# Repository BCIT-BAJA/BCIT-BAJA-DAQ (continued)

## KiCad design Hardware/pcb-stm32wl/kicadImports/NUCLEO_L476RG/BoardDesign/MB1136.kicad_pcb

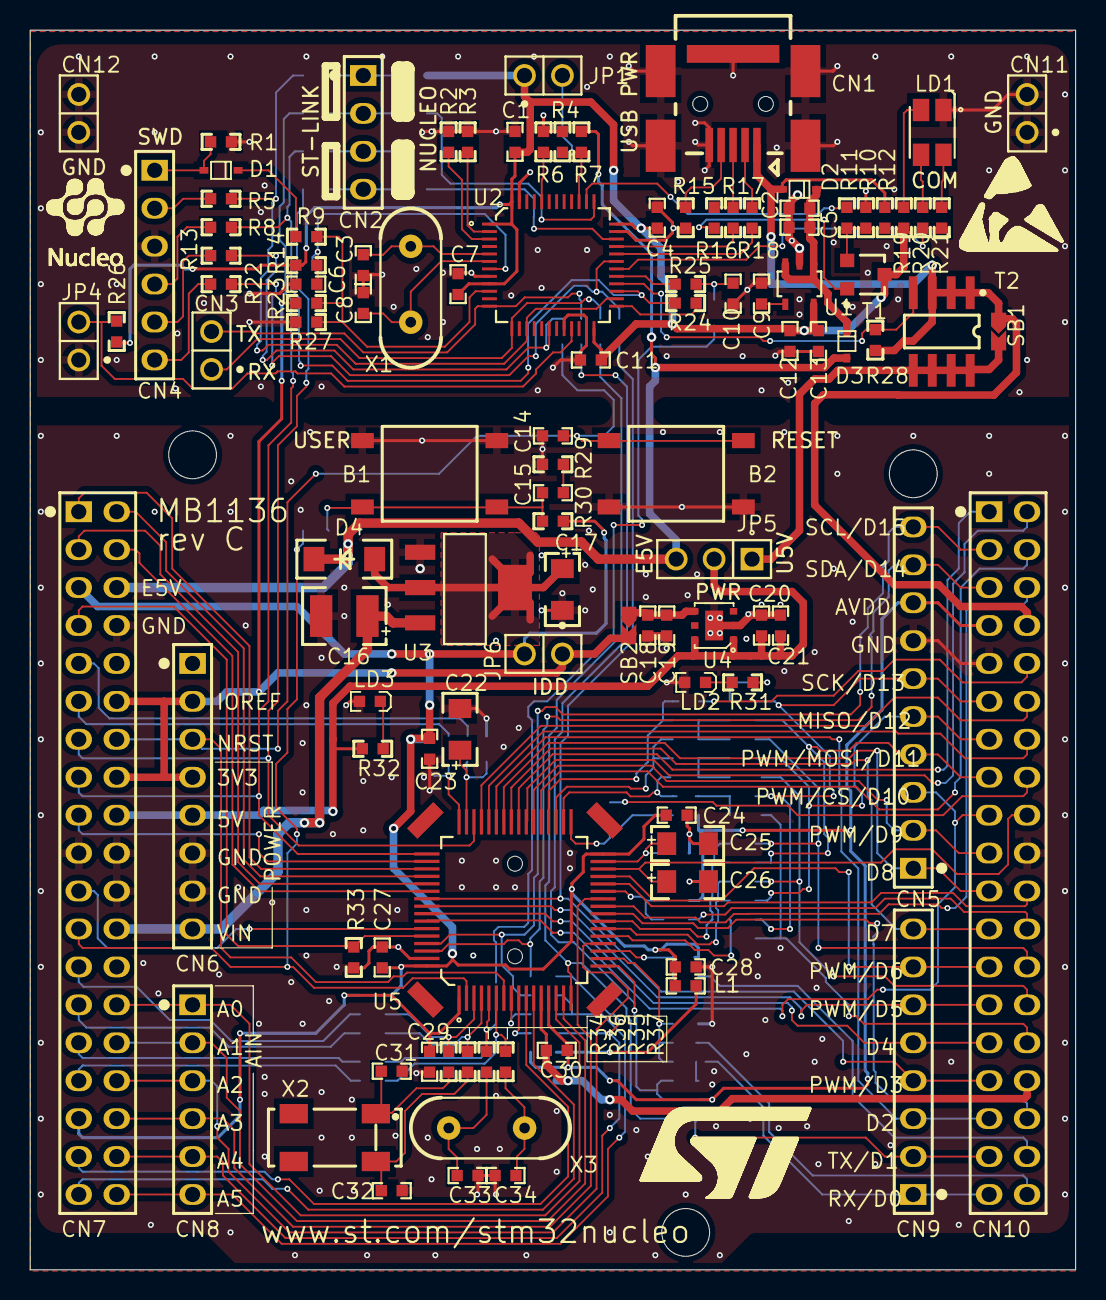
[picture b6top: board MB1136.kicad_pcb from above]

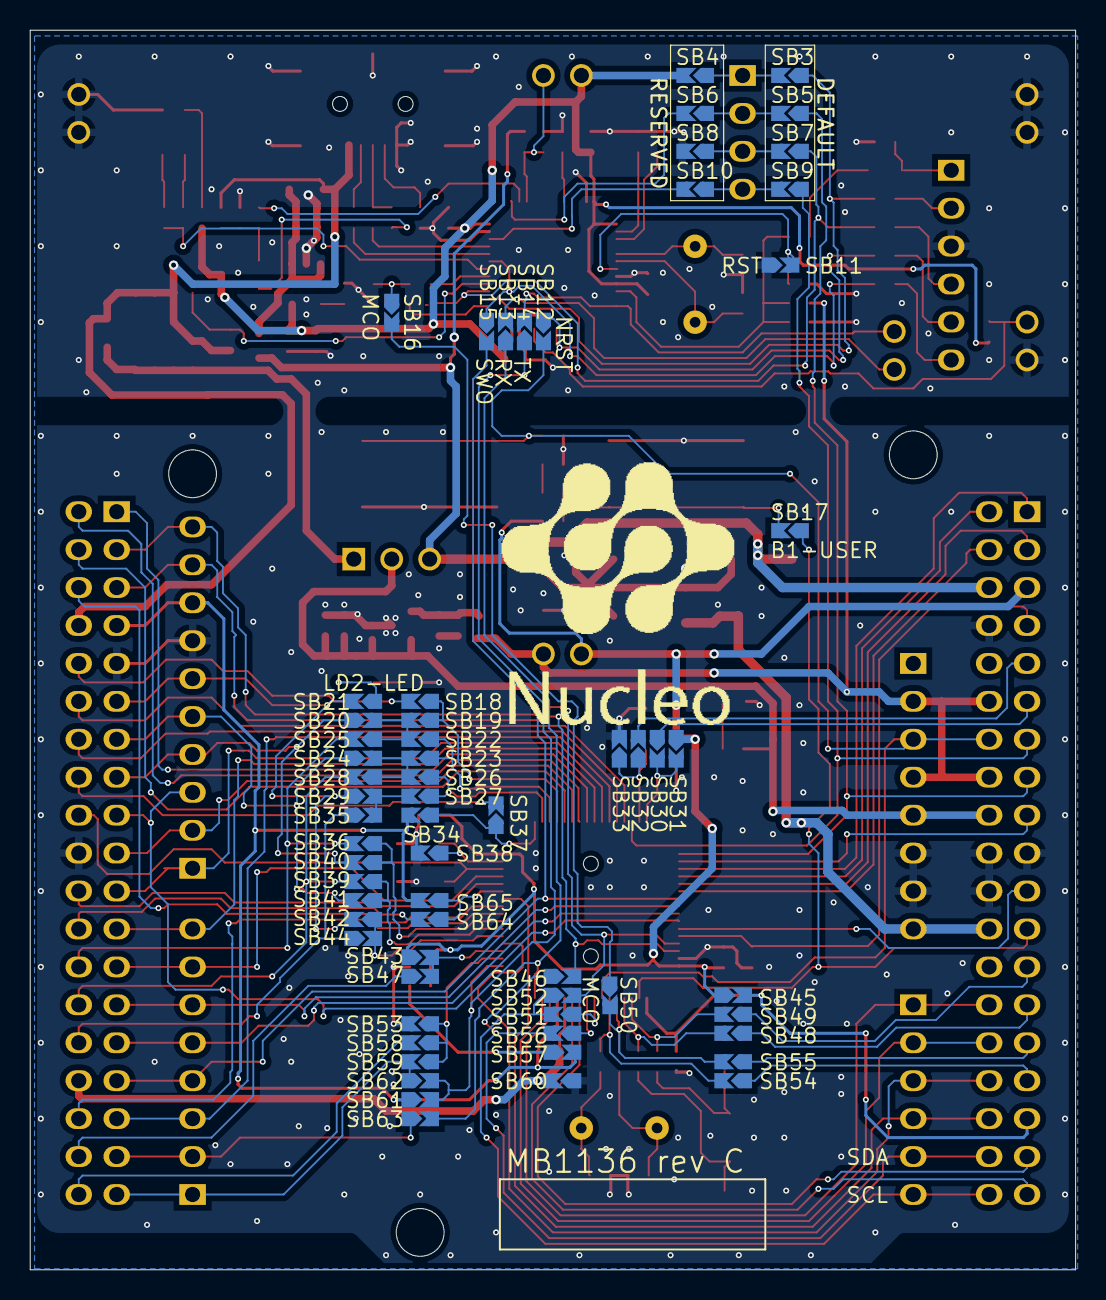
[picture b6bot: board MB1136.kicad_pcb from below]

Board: 2 copper layers, 70.0 x 83.0 mm, 176 parts (64 on the bottom side), 152 nets.

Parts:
B1: USER (Blue); PB10
B2: TD-0341 [RESET/Black]; PB10
C1, C4, C5, C6, C7, C11, C12, C14, C15, C19, C20, C23, C24, C27, C28, C30: 100nF; 0603C
C2, C13, C18, C21, C29: 1uF_X5R_0603; 0603C
C3, C8, C10: 20pF; 0603C
C9: 10nF_X7R_0603; 0603C
C16: 10uF(25V); TAN-B
C17: 10uF; TAN-A
C22, C25, C26: 2.2uF; TAN-A
C31, C32: 10pF[N/A]; 0603C
C33, C34: 20pF[N/A]; 0603C
CN1: 5075BMR-05-SM; USB-MINI-B-SMD
CN2: Header 4; 1*4
CN3, CN11, CN12: SIP2/2.54
CN4: Header 6X1; 1*6P
CN5: Header 10X1_Female; 1*10P_FEMALE
CN6, CN9: Header 8X1_Female; 1*8P_FEMALE
CN7, CN10: Header 19X2; 2*19P
CN8: Header 6X1_Female; 1*6P_FEMALE
D1, D2, D3: BAT60JFILM; SOD323/A
D4: STPS2L30A; SMA
Designator1: Comment; NUCLEO_black 0.5cm
Designator2: Comment; LOGO ESD
Designator4: Comment; NUCLEO_black 2cm
Designator22: Comment; ST_LOGO_10mm
JP1, JP4, JP6: SIP2/2.54
JP5: SIP3
L1: BEAD; 0603L
LD1: LD_BICOLOR_CMS; HSMF-A201
LD2: Green; 0603D
LD3: RED; 0603D
R1, R2, R3, R12, R26, R33: 10K; 0603R
R4, R23, R27, R28, R30: 4K7; 0603R
R5, R8, R13, R22: 22; 0603R
R6, R14, R15: 100K; 0603R
R7: 2K7; 0603R
R9, R11, R20, R21, R24, R25, R29: 100; 0603R
R10: 36K; 0603R
R16: 1K5; 0603R
R17, R18, R19: 0; 0603R
R31: 510; 0603R
R32: 1K; 0603R
R34, R35, R36, R37: [N/A]; 0603R
SB1, SB2, SB3, SB4, SB5, SB6, SB7, SB8, SB9, SB10, SB11, SB12, SB13, SB14, SB15, SB16, SB17, SB18, SB19, SB20, SB21, SB22, SB23, SB24, SB25, SB26, SB27, SB28, SB29, SB30, SB31, SB32, SB33, SB34, SB35, SB36, SB37, SB38, SB39, SB40, SB41, SB42, SB43, SB44, SB45, SB46, SB47, SB48, SB49, SB50, SB51, SB52, SB53, SB54, SB55, SB56, SB57, SB58, SB59, SB60, SB61, SB62, SB63, SB64, SB65: Circuit Breaker; JP2_SMD
T1: 9013; SOT-23
T2: STS7PF30L; SO8
U1: LD3985M33R; SOT-23-5L
U2: STM32F103CBT6; QFP48 7X7
U3: LD1117S50TR; SOT-223
U4: LD39050PU33R; DFN6(3X3)
U5: MCU_LQFP64; LQFP64
X1: 8MHz(12pF); XTAL1
X2: 32.768K[N/A]; XTAL_4SM_8X3R8
X3: 8MHz(16pF)[N/A]; XTAL1

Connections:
+3V3: CN6.2, CN6.4, CN7.12, CN7.16, JP6.1, R23.1, SB2.2
+3V3_ST_LINK: C1.2, C4.2, C7.2, C11.2, C12.2, C13.1, JP1.1, R14.2, R19.2, R26.1, SB4.2, T1.3, U1.5, U2.1, U2.9, U2.24, U2.36, U2.48
+5V: C20.2, C21.1, CN6.5, CN7.18, JP5.2, R32.2, U4.1, U4.6
AGND: C30.2, CN10.32, SB60.2, U5.12
AIN_1: R9.2, R23.2, R27.2, U2.10
AVDD: C30.1, CN5.8, CN10.7, SB34.2, SB57.2, SB61.1, SB65.2, U5.13
BOOT0: CN7.7, R33.1, U5.60
E5V: CN7.6, D3.1, D4.2, JP5.3, R7.1
GND: B1.1, B1.4, B2.1, B2.4, C1.1, C2.1, C3.2, C4.1, C5.1, C6.1, C7.1, C8.2, C9.1, C10.2, C11.1, C12.1, C13.2, C14.1, C16.2, C17.2, C18.2, C19.1, C20.1, C21.2, C22.2, C23.2, C24.2, C25.2, C26.2, C27.2, C28.2, C29.2, C31.2, C32.2, C33.2, C34.2, CN1.5, CN1.6, CN4.3, CN5.7, CN6.6, CN6.7, CN7.8, CN7.19, CN7.20, CN7.22, CN10.9, CN10.20, CN11.1, CN11.2, CN12.1, CN12.2, JP4.1, LD1.1, LD2.2, LD3.2, R1.2, R2.1, R3.1, R4.2, R6.1, R10.1, R15.2, R27.1, R29.1, R33.2, SB8.2, SB11.1, SB33.2, SB38.2, SB53.2, SB60.1, U1.2, U2.8, U2.20, U2.23, U2.35, U2.47, U3.1, U4.0, U4.2, U5.63
LED_STLINK: R20.1, R21.1, U2.30
MCO: SB16.2, SB50.1
NRST: B2.2, B2.3, C14.2, CN6.3, CN7.14, SB12.2, U5.7
NetB1_2: B1.2, B1.3, C15.2, R30.1, SB17.2
NetC2_2: C2.2, C5.2, D2.2, D3.2, U1.1, U1.3
NetC9_2: C9.2, U1.4
NetC10_1: C10.1, R25.2, SB16.1
NetC15_1: C15.1, R29.2
NetC17_1: C17.1, D4.1, U3.2, U3.4
NetC18_1: C18.1, C19.2, SB2.1, U4.4
NetC22_1: C22.1, SB32.1, SB33.1, U5.47
NetC25_1: C25.1, SB38.1, U5.31
NetC31_1: C31.1, R34.1, X2.1
NetC32_1: C32.1, R36.1, X2.4
NetC33_1: C33.1, R35.2, X3.2
NetC34_1: C34.1, R37.2, X3.1
NetCN1_2: CN1.2, R18.1
NetCN1_3: CN1.3, R16.1, R17.1
NetCN1_4: CN1.4, R15.1
NetCN2_1: CN2.1, SB3.2, SB4.1
NetCN2_2: CN2.2, SB5.2, SB6.1
NetCN2_3: CN2.3, SB7.2, SB8.1
NetCN2_4: CN2.4, SB9.2, SB10.1
NetCN4_1: CN4.1, D1.1, R1.1
NetCN4_2: CN4.2, R5.1
NetCN4_4: CN4.4, R8.1
NetCN4_5: CN4.5, R13.1
NetCN4_6: CN4.6, R22.1
NetCN5_4: CN5.4, CN10.15, SB20.1, SB40.2
NetCN5_5: CN5.5, CN10.13, SB24.1, SB41.2
NetCN5_6: CN5.6, CN10.11, SB21.2, SB29.1, SB42.2
NetCN7_25: CN7.25, SB49.1
NetCN7_27: CN7.27, SB48.1
NetCN7_29: CN7.29, SB55.1
NetCN7_31: CN7.31, SB54.1
NetCN7_36: CN7.36, CN8.5, SB46.1, SB56.2
NetCN7_38: CN7.38, CN8.6, SB51.2, SB52.1
NetCN10_26: CN10.26, SB25.2, SB36.2
NetCN10_28: CN10.28, SB28.2, SB39.2
NetCN10_30: CN10.30, SB35.1, SB44.1
NetD1_2: D1.2, R9.1
NetJP1_2: JP1.2, R4.1, R7.2, U2.39
NetJP4_2: JP4.2, R26.2, U2.21
NetJP5_1: JP5.1, SB1.2, T2.5, T2.6, T2.7, T2.8
NetL1_2: L1.2, SB57.1
NetLD1_2: LD1.2, R21.2
NetLD1_3: LD1.3, R20.2
NetLD1_4: LD1.4, R19.1
NetLD2_1: LD2.1, R31.2
NetLD3_1: LD3.1, R32.1
NetR2_2: R2.2, U2.3
NetR3_2: R3.2, U2.2
NetR6_2: R6.2, U2.44
NetR10_2: R10.2, R11.1, R12.1, T1.2
NetR16_2: R16.2, T1.1
NetR25_1: R25.1, U2.29
NetR28_2: R28.2, T2.4, U2.28
NetR31_1: R31.1, SB21.1
NetSB13_1: SB13.1, SB63.2, U5.16
NetSB14_1: SB14.1, SB61.2, SB62.2, U5.17
NetSB18_1: SB18.1, SB19.1, U5.36
NetSB22_1: SB22.1, SB23.1, U5.35
NetSB26_1: SB26.1, SB27.1, U5.34
NetSB30_2: SB30.2, SB31.2, U5.48
NetSB34_1: SB34.1, SB37.1, U5.33
NetSB43_2: SB43.2, SB47.2, U5.19
NetSB53_1: SB53.1, SB58.1, SB59.1, U5.18
NetSB64_1: SB64.1, SB65.1, U5.27
OSC_IN: C3.1, U2.5, X1.2
OSC_OUT: C8.1, U2.6, X1.1
PA0: CN7.28, CN8.1, U5.14
PA1: CN7.30, CN8.2, U5.15
PA2: CN9.2, CN10.35, SB63.1
PA3: CN9.1, CN10.37, SB59.2, SB62.1
PA4: CN7.32, CN8.3, U5.20
PA5: SB42.1, SB44.2, U5.21
PA6: SB39.1, SB41.1, U5.22
PA7: SB36.1, SB40.1, U5.23
PA8: CN9.8, CN10.23, U5.41
PA9: CN5.1, CN10.21, U5.42
PA10: CN9.3, CN10.33, U5.43
PA11: CN10.14, U5.44
PA12: CN10.12, U5.45
PA13: CN7.13, SB9.1, U5.46
PA14: CN7.15, SB5.1, U5.49
PA15: CN7.17, U5.50
PB0: CN7.34, CN8.4, U5.26
PB1: CN10.24, SB64.2
PB2: CN10.22, U5.28
PB3: CN9.4, CN10.31, SB15.2, U5.55
PB4: CN9.6, CN10.27, U5.56
PB5: CN9.5, CN10.29, U5.57
PB6: CN5.3, CN10.17, U5.58
PB7: CN7.21, U5.59
PB8: CN5.10, CN10.3, SB52.2, U5.61
PB9: CN5.9, CN10.5, SB46.2, U5.62
PB10: CN9.7, CN10.25, U5.29
PB11: C26.1, CN10.18, U5.30
PB12: CN10.16, SB37.2
PB13: SB27.2, SB29.2, SB35.2
PB14: SB23.2, SB24.2, SB26.2, SB28.1
PB15: SB19.2, SB20.2, SB22.2, SB25.1
PC0: SB51.1, U5.8
PC1: SB56.1, U5.9
PC2: CN7.35, U5.10
PC3: CN7.37, U5.11
PC4: CN10.34, U5.24
PC5: CN10.6, U5.25
PC6: CN10.4, U5.37
PC7: CN5.2, CN10.19, U5.38
PC8: CN10.2, U5.39
PC9: CN10.1, U5.40
PC10: CN7.1, U5.51
PC11: CN7.2, U5.52
PC12: CN7.3, U5.53
PC13: CN7.23, SB17.1, U5.2
PC14: R34.2, SB49.2, U5.3
PC15: R36.2, SB48.2, U5.4
PD2: CN7.4, U5.54
PD8: CN10.10, SB18.2
PF0: R35.1, SB50.2, SB55.2, U5.5
PF1: R37.1, SB54.2, U5.6
PF4: CN10.38, SB58.2
PF5: CN10.36, SB47.1
PF6: CN7.9, SB32.2
PF7: CN7.11, SB30.1
STLINK_RX: CN3.1, SB13.2, U2.13
STLINK_TX: CN3.2, SB14.2, U2.12
STM_JTCK: SB6.2, U2.37
STM_JTMS: SB10.2, U2.34
STM_RST: C6.2, R14.1, SB11.2, U2.7
T_JTCK: R5.2, SB3.1, U2.15, U2.26
T_JTMS: R8.2, R24.2, SB7.1, U2.27
T_NRST: R13.2, SB12.1, U2.18
T_SWDIO_IN: R24.1, U2.25
T_SWO: R22.2, SB15.1, U2.31
U5V: CN1.1, CN10.8, D2.1, R12.2, R28.1, SB1.1, T2.1, T2.2, T2.3
USB_CTRL: R11.2, U2.38
USB_DM: R18.2, U2.32
USB_DP: R17.2, U2.33
VBAT/VLCD: C29.1, CN7.33, SB45.2, U5.1
VDD: C23.1, C24.1, C27.1, C28.1, CN7.5, JP6.2, L1.1, R30.2, SB31.1, SB43.1, SB45.1, U5.32, U5.64
VIN: C16.1, CN6.8, CN7.24, U3.3

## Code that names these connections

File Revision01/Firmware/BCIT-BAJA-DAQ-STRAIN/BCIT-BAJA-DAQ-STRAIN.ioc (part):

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Mcu.Name=STM32L476R(C-E-G)Tx
Mcu.Package=LQFP64
Mcu.UserName=STM32L476RGTx
PA0.GPIOParameters=GPIO_Label
PA0.GPIO_Label=AIn_StrainV_1
PA0.Signal=ADCx_IN5
PA1.GPIOParameters=GPIO_Label
PA1.GPIO_Label=AIn_StrainV_2
PA1.Signal=ADCx_IN6
PA10.GPIOParameters=GPIO_Label
PA10.GPIO_Label=GPIO_Extra_SPI_CS_N
PA10.Signal=GPIO_Output
PA13\ (JTMS-SWDIO).GPIOParameters=GPIO_Label
PA13\ (JTMS-SWDIO).GPIO_Label=TMS
PA13\ (JTMS-SWDIO).Mode=Serial_Wire
PA13\ (JTMS-SWDIO).Signal=SYS_JTMS-SWDIO
PA14\ (JTCK-SWCLK).GPIOParameters=GPIO_Label
PA14\ (JTCK-SWCLK).GPIO_Label=TCK
PA14\ (JTCK-SWCLK).Mode=Serial_Wire
PA14\ (JTCK-SWCLK).Signal=SYS_JTCK-SWCLK
PA15\ (JTDI).GPIOParameters=GPIO_Label
PA15\ (JTDI).GPIO_Label=GPIO_StrainV_Enable_5VTolerant_N
PA15\ (JTDI).Signal=GPIO_Output
PA2.GPIOParameters=GPIO_Speed,GPIO_PuPd,GPIO_Label,GPIO_Mode
PA2.GPIO_Label=USART_TX
PA2.GPIO_Mode=GPIO_MODE_AF_PP
PA2.GPIO_PuPd=GPIO_NOPULL
PA2.GPIO_Speed=GPIO_SPEED_FREQ_VERY_HIGH
PA2.Mode=Asynchronous
PA2.Signal=USART2_TX
PA3.GPIOParameters=GPIO_Speed,GPIO_PuPd,GPIO_Label,GPIO_Mode
PA3.GPIO_Label=USART_RX
PA3.GPIO_Mode=GPIO_MODE_AF_PP
PA3.GPIO_PuPd=GPIO_NOPULL
PA3.GPIO_Speed=GPIO_SPEED_FREQ_VERY_HIGH
PA3.Mode=Asynchronous
PA3.Signal=USART2_RX
PA4.GPIOParameters=GPIO_Label
PA4.GPIO_Label=AIn_StrainV_3
PA4.Signal=ADCx_IN9
PA5.GPIOParameters=GPIO_Speed,GPIO_PuPd,GPIO_Label,GPIO_ModeDefaultOutputPP
PA5.GPIO_Label=LD2 [green Led]
PA5.GPIO_ModeDefaultOutputPP=GPIO_MODE_OUTPUT_PP
PA5.GPIO_PuPd=GPIO_NOPULL
PA5.GPIO_Speed=GPIO_SPEED_FREQ_LOW
PA5.Signal=GPIO_Output
PA6.GPIOParameters=GPIO_Label
PA6.GPIO_Label=AIn_StrainV_6
PA6.Signal=ADCx_IN11
PB0.GPIOParameters=GPIO_Label
PB0.GPIO_Label=AIn_StrainV_4
PB0.Signal=ADCx_IN15
PB1.GPIOParameters=GPIO_Label
PB1.GPIO_Label=AIn_StrainV_7
PB1.Signal=ADCx_IN16
PB13.Mode=Full_Duplex_Master
PB13.Signal=SPI2_SCK
PB14.Mode=Full_Duplex_Master
PB14.Signal=SPI2_MISO
PB15.Mode=Full_Duplex_Master
PB15.Signal=SPI2_MOSI
PB3\ (JTDO-TRACESWO).GPIOParameters=GPIO_Label
PB3\ (JTDO-TRACESWO).GPIO_Label=SWO
PB3\ (JTDO-TRACESWO).Signal=SYS_JTDO-SWO
PB6.GPIOParameters=GPIO_Label
PB6.GPIO_Label=GPInterruptPB6_MPU
PB6.Signal=GPXTI6
PB8.GPIOParameters=GPIO_Label
PB8.GPIO_Label=GPIO_ANT_SPI_CS_N
PB8.Signal=GPIO_Output
PC0.GPIOParameters=GPIO_Label
PC0.GPIO_Label=AIn_BatteryV
PC0.Signal=GPIO_Analog
PC1.GPIOParameters=GPIO_Label
PC1.GPIO_Label=GPIO_BatteryV_Enable
PC1.Signal=GPIO_Analog
PC13.GPIOParameters=GPIO_PuPd,GPIO_Label,GPIO_ModeDefaultEXTI
PC13.GPIO_Label=B1 [Blue PushButton]
PC13.GPIO_ModeDefaultEXTI=GPIO_MODE_IT_FALLING
PC13.GPIO_PuPd=GPIO_NOPULL
PC13.Signal=GPXTI13
PC14-OSC32_IN\ (PC14).Mode=LSE-External-Oscillator
PC14-OSC32_IN\ (PC14).Signal=RCC_OSC32_IN
PC15-OSC32_OUT\ (PC15).Mode=LSE-External-Oscillator
PC15-OSC32_OUT\ (PC15).Signal=RCC_OSC32_OUT
PC4.GPIOParameters=GPIO_Label
PC4.GPIO_Label=AIn_StrainV_8
PC4.Signal=ADCx_IN13
PC5.GPIOParameters=GPIO_Label
PC5.GPIO_Label=AIn_StrainV_5
PC5.Signal=ADCx_IN14
PC6.GPIOParameters=GPIO_Label
PC6.GPIO_Label=GPIO_ANT_Enable
PC6.Signal=GPIO_Output
PC7.GPIOParameters=GPIO_Label
PC7.GPIO_Label=GPIO_MPU_SPI_CS_N
PC7.Signal=GPIO_Output
PC8.GPIOParameters=GPIO_Label
PC8.GPIO_Label=GPInterruptPC8_ANT_DIO0
PC8.Signal=GPXTI8
PC9.GPIOParameters=GPIO_Label
PC9.GPIO_Label=GPIO_ANT_Reset
PC9.Signal=GPIO_Output
PH0-OSC_IN\ (PH0).Signal=RCC_OSC_IN
PH1-OSC_OUT\ (PH1).Signal=RCC_OSC_OUT
RCC.HSE_VALUE=8000000
RCC.SYSCLKFreq_VALUE=80000000
RCC.SYSCLKSource=RCC_SYSCLKSOURCE_PLLCLK
board=NUCLEO-L476RG
boardIOC=true

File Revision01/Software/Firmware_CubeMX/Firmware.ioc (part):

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Mcu.Name=STM32L476R(C-E-G)Tx
Mcu.Package=LQFP64
Mcu.UserName=STM32L476RGTx
PA0.GPIOParameters=GPIO_Label
PA0.GPIO_Label=AIn_StrainV_1
PA0.Signal=ADCx_IN5
PA1.GPIOParameters=GPIO_Label
PA1.GPIO_Label=AIn_StrainV_2
PA1.Signal=ADCx_IN6
PA10.GPIOParameters=PinState,GPIO_Label
PA10.GPIO_Label=GPIO_Extra_SPI_CS
PA10.PinState=GPIO_PIN_SET
PA10.Signal=GPIO_Output
PA15\ (JTDI).GPIOParameters=PinState,GPIO_PuPd,GPIO_Label,GPIO_ModeDefaultOutputPP
PA15\ (JTDI).GPIO_Label=GPIO_StrainV_Enable_5VTolerant_N
PA15\ (JTDI).GPIO_ModeDefaultOutputPP=GPIO_MODE_OUTPUT_OD
PA15\ (JTDI).GPIO_PuPd=GPIO_NOPULL
PA15\ (JTDI).PinState=GPIO_PIN_SET
PA15\ (JTDI).Signal=GPIO_Output
PA2.Mode=Asynchronous
PA2.Signal=USART2_TX
PA3.Mode=Asynchronous
PA3.Signal=USART2_RX
PA4.GPIOParameters=GPIO_Label
PA4.GPIO_Label=AIn_StrainV_3
PA4.Signal=ADCx_IN9
PA5.GPIOParameters=PinState,GPIO_Label
PA5.GPIO_Label=GPIO_LED2
PA5.PinState=GPIO_PIN_SET
PA5.Signal=GPIO_Output
PA6.GPIOParameters=GPIO_Label
PA6.GPIO_Label=AIn_StrainV_6
PA6.Signal=ADCx_IN11
PB0.GPIOParameters=GPIO_Label
PB0.GPIO_Label=AIn_StrainV_4
PB0.Signal=ADCx_IN15
PB1.GPIOParameters=GPIO_Label
PB1.GPIO_Label=AIn_StrainV_7
PB1.Signal=ADCx_IN16
PB13.Mode=Full_Duplex_Master
PB13.Signal=SPI2_SCK
PB14.Mode=Full_Duplex_Master
PB14.Signal=SPI2_MISO
PB15.Mode=Full_Duplex_Master
PB15.Signal=SPI2_MOSI
PB6.GPIOParameters=GPIO_Label
PB6.GPIO_Label=GPInterruptPB6_MPU
PB6.Signal=GPXTI6
PB8.GPIOParameters=PinState,GPIO_Label
PB8.GPIO_Label=GPIO_ANT_SPI_CS
PB8.PinState=GPIO_PIN_SET
PB8.Signal=GPIO_Output
PC0.GPIOParameters=GPIO_Label
PC0.GPIO_Label=AIn_BatteryV
PC0.Signal=ADCx_IN1
PC13.GPIOParameters=GPIO_Label
PC13.GPIO_Label=BluePB_Down_N
PC13.Signal=GPIO_Input
PC4.GPIOParameters=GPIO_Label
PC4.GPIO_Label=AIn_StrainV_8
PC4.Signal=ADCx_IN13
PC5.GPIOParameters=GPIO_Label
PC5.GPIO_Label=AIn_StrainV_5
PC5.Signal=ADCx_IN14
PC6.GPIOParameters=GPIO_Label
PC6.GPIO_Label=GPIO_ANT_Enable
PC6.Signal=GPIO_Output
PC7.GPIOParameters=PinState,GPIO_Label
PC7.GPIO_Label=GPIO_MPU_SPI_CS_N
PC7.PinState=GPIO_PIN_SET
PC7.Signal=GPIO_Output
PC8.GPIOParameters=GPIO_Label
PC8.GPIO_Label=GPInterruptPC8_ANT_DIO0
PC8.Signal=GPXTI8
PC9.GPIOParameters=GPIO_Label
PC9.GPIO_Label=GPIO_ANT_Reset
PC9.Signal=GPIO_Output
RCC.HSE_VALUE=8000000
board=NUCLEO-L476RG

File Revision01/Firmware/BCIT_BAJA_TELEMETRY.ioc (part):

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Mcu.Name=STM32L476R(C-E-G)Tx
Mcu.Package=LQFP64
Mcu.UserName=STM32L476RGTx
PA0.Signal=ADCx_IN5
PA1.Signal=ADCx_IN6
PA13\ (JTMS-SWDIO).GPIOParameters=GPIO_Label
PA13\ (JTMS-SWDIO).GPIO_Label=TMS
PA13\ (JTMS-SWDIO).Mode=Serial_Wire
PA13\ (JTMS-SWDIO).Signal=SYS_JTMS-SWDIO
PA14\ (JTCK-SWCLK).GPIOParameters=GPIO_Label
PA14\ (JTCK-SWCLK).GPIO_Label=TCK
PA14\ (JTCK-SWCLK).Mode=Serial_Wire
PA14\ (JTCK-SWCLK).Signal=SYS_JTCK-SWCLK
PA2.GPIOParameters=GPIO_Speed,GPIO_PuPd,GPIO_Label,GPIO_Mode
PA2.GPIO_Label=USART_TX
PA2.GPIO_Mode=GPIO_MODE_AF_PP
PA2.GPIO_PuPd=GPIO_NOPULL
PA2.GPIO_Speed=GPIO_SPEED_FREQ_VERY_HIGH
PA2.Mode=Asynchronous
PA2.Signal=USART2_TX
PA3.GPIOParameters=GPIO_Speed,GPIO_PuPd,GPIO_Label,GPIO_Mode
PA3.GPIO_Label=USART_RX
PA3.GPIO_Mode=GPIO_MODE_AF_PP
PA3.GPIO_PuPd=GPIO_NOPULL
PA3.GPIO_Speed=GPIO_SPEED_FREQ_VERY_HIGH
PA3.Mode=Asynchronous
PA3.Signal=USART2_RX
PA5.Signal=ADCx_IN10
PA6.Signal=GPIO_Analog
PA7.Signal=ADCx_IN12
PA8.Signal=GPXTI8
PA9.Signal=GPIO_Output
PB0.Signal=GPIO_Output
PB1.Signal=ADCx_IN16
PB10.Signal=GPIO_Output
PB3\ (JTDO-TRACESWO).GPIOParameters=GPIO_Label
PB3\ (JTDO-TRACESWO).GPIO_Label=SWO
PB3\ (JTDO-TRACESWO).Signal=SYS_JTDO-SWO
PB6.Signal=GPXTI6
PB7.Signal=GPIO_Output
PC0.Signal=ADCx_IN1
PC1.Signal=ADCx_IN2
PC11.Signal=GPIO_Output
PC12.Signal=GPIO_Output
PC13.GPIOParameters=GPIO_PuPd,GPIO_Label,GPIO_ModeDefaultEXTI
PC13.GPIO_Label=B1 [Blue PushButton]
PC13.GPIO_ModeDefaultEXTI=GPIO_MODE_IT_FALLING
PC13.GPIO_PuPd=GPIO_NOPULL
PC13.Signal=GPXTI13
PC14-OSC32_IN\ (PC14).Mode=LSE-External-Oscillator
PC14-OSC32_IN\ (PC14).Signal=RCC_OSC32_IN
PC15-OSC32_OUT\ (PC15).Mode=LSE-External-Oscillator
PC15-OSC32_OUT\ (PC15).Signal=RCC_OSC32_OUT
PC2.Signal=GPIO_Analog
PC4.Signal=ADCx_IN13
PC5.Signal=ADCx_IN14
PC6.GPIOParameters=GPIO_Label
PC6.GPIO_Label=strainEN
PC6.Signal=GPIO_Output
PC7.Signal=GPIO_Analog
PC9.GPIOParameters=GPIO_Label
PC9.GPIO_Label=V_batt_en
PC9.Signal=GPIO_Output
PH0-OSC_IN\ (PH0).Signal=RCC_OSC_IN
PH1-OSC_OUT\ (PH1).Signal=RCC_OSC_OUT
RCC.HSE_VALUE=8000000
RCC.SYSCLKFreq_VALUE=80000000
RCC.SYSCLKSource=RCC_SYSCLKSOURCE_PLLCLK
board=NUCLEO-L476RG
boardIOC=true

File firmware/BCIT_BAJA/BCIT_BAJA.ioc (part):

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Mcu.Name=STM32L476R(C-E-G)Tx
Mcu.Package=LQFP64
Mcu.UserName=STM32L476RGTx
PA0.Signal=GPIO_Output
PA1.Signal=GPIO_Output
PB0.Signal=GPIO_Analog
PB1.Signal=GPIO_Analog
PB13.Mode=Full_Duplex_Master
PB13.Signal=SPI2_SCK
PB14.Mode=Full_Duplex_Master
PB14.Signal=SPI2_MISO
PB15.Mode=Full_Duplex_Master
PB15.Signal=SPI2_MOSI
PB2.Signal=GPIO_Analog
PC0.Signal=ADCx_IN1
PC1.Signal=GPIO_Output
PC2.Signal=GPIO_Output
PC3.Signal=GPIO_Output
PC4.Signal=GPIO_Output
PC5.Signal=GPIO_Analog
PC6.Signal=GPIO_Output
PC7.Signal=GPIO_Output
PC8.Signal=GPIO_Output
PC9.Signal=GPIO_Output
RCC.HSE_VALUE=8000000
board=custom

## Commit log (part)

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2025-03-01 Added hardware design files
2025-03-01 Create firmwareREADME
2025-03-04 added an stm32
2025-03-04 adding stm32 attempt 2
2025-03-09 template re-uploaded
2025-03-10 deleted some components today, finished selecting BUCK converter components for 5V
2025-03-10 changed todolist
2025-03-10 selected GYROSCOPE COMPONENTS
2025-03-11 all new components placed, not wired
2025-03-11 ALL BOM components have been added with manufacturing part nunmber, alongside distributor link
2025-03-12 wired, and selected capacitors. Not sure if they are correct as there was nothing in datasheet for it
2025-03-13 rewried circuit to account ofr small details
2025-03-15 removing oldfile
2025-03-15 added USB-C for possibility of usage
2025-03-16 New commit message
2025-03-16 Both mosfet will not be added into circuit. Both IMU and ANTENNA have sleep mode, which is in the micro to milliamp current usage range. Add in capacitor will optimize the system slighty, however the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
    to size for capcitor, we need to know oscillations of buck converter(which is complicated) and is already filtered at output of buck converter. So, I will avoid adding in this.
2025-03-18 Renamed root Hardware/pcb-* folder to Hardware/Revision01; Edited .gitignore files & folders
2025-03-18 . Slight style changes to capacitors, ground symbols; ignored *.swp files
2025-03-19 added in some additional notes on review
2025-03-22 Mainly verified and fixed peripheral component selection MOSFET-WIREOUT - DONE ANTENNA WIRE-OUT - DONE ADC WIRE-OUT - DONE - found error in ADC wireout, EP was left unconnected - notes on pins I foun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
    CHECK COMPONENT SELECTION ON
    MOSFET - Done
    Need to pick 100K component and 33K components - Done
    ADC - Done
    ANTENNA - Done
    IMU - done
2025-03-23 . Completed MCU schematic & imported hierarchical model pins
2025-03-23 added battery specifications in main sheet
2025-03-23 . Fixed MCU sheet pins neglecting Button1, Button2, and LED2.
2025-03-23 footprint added for nucleo board
    To do before PCB LAYOUT
    clean up schematic
    wire-accross sheets
    Improve annotation ordering
    Perform ERC check
    Ensure all components have footprints
2025-03-25 started wiring modules together
2025-03-25 implemented feedback
2025-03-28 Added new LDO to fit into new battery range.
2025-03-28 Added new LDO to fit into battery range that feeds into MCU, make sure to remove power jumper wire before connecting. Completed ERC check
    Still have to put on footprints for some components when doing PCB layout
2025-03-29 todays review session
2025-03-30 added back powerflags back for ERC
2025-04-26 added connection for ADC PSW
2025-04-27 Stimulated new battery measurement circuit(Which uses a load switch)
2025-04-30 Reworked Controller sheet to nucleo L476RG
2025-04-30 all 3d models imported, except for antenna which cannot be found
2025-05-03 testing github
2025-05-03 feat(pcb layout)- grouped components by function in general area they will be placed in
2025-05-08 fixed some ERC errors related to JUMPERS
2025-05-12 differential pairs setup, ready to wire on third layer.
2025-05-14 some feedback implemented, MISO/MOSI SIWTCHED, GPIO_USB_5V FIXED, COMMENTS REGARDING ALTERNATIVE ADC's, and PCB CONNECTED TO EXTERNAL GND added
2025-05-16 Finished up small things(on schematic layout)
    -Connector pins switched such that GND is pin 1
    -used KICAD feature to indicate ACTIVE LOW
    -polyFuse added to each StrainGauge
    -Added Grounded Mounting holes connects to external GND(outside of PCB)
2025-05-19 schematic wiring, and LT-SPICE simulations on strain gauge - Added buffer with offset at 1.66V to instrumentation amplifier to ensure -20-20mv range can be read - Added caps to Instrumentation Amplif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
2025-05-21 Started working on PART B schematic, making small changes on PART A
    ADC uncertainty calculated to be 1.22%
    Added External GPIO's that may or may not use
    start/stop, indication RGB leds
    Started working on PART B schematic on ALTIUM, properly imported components with footprints
2025-05-24 part B schematic complete:
    - fuse added
    - input terminals protected against S.C
2025-05-27 Added protection ciruitry and completed most of LAYOUT for PART A
    - Added SC protection against AMPLIFIER input circuitry
    -Completed PCB layout for STRAIN AMPLIFIER V1
    -Internal temperature sensor exists inside STM32
    -added schottky diodes to clamp over/undervoltage to protect ADC
    - Analog layer layout complete
    - Power circuitry layed out
2025-06-01 Schematic changes - Remove LDO - find new battery holder - repicked power switch - voltage divider value changed R2=5K - branch fuses moved back to main to ensure wires stay downstream
2025-06-04 Small details on PART B, restarting component placement on PART A
2025-06-05 COMPONENT LAYOUT COMPLETE
2025-06-06 small changes to ROUTING
2025-06-08 meeting stuff
2025-06-09 forgot to save last commit
2025-06-16 not sure what is here
2025-06-17 PART A - sent to manufacturer for review
    ALL NUCLEO PINS configured/verified ON STM32IDE,
    verified battery INPUT WORKS - note 5V rail is 3.9V utilizing 10V battery
    Removed floating traces
    Improved silkscreen
2025-06-18 REWIRING SCHEMATIC OVER HEAT CONCERN - picked and wired buck-converter - started FMEA analysis
2025-06-23 random stuff
2025-06-25 Removed, ignored temporary files & folders.
2025-06-25 Changed the .gitignore to all #auto_saved_files#
2025-06-27 lost altium file, testing to see if commits
2025-06-28 review 2 implemented
    - Made mounting holes symmetrical
    - Buck enable 0 ohm resistor error fixed
2025-07-03 Un-deleted firmware/antenna_bitrate.ods
2025-07-06 Changed SW1 to be four pins, so that the LED & switch power have separate wires.
2025-07-06 Excluded 3 warnings: Pins of type Unspecified and Passive are connected
2025-07-06 ERC Warnings: 21
    - Replaced 8x Strain Gauge JST Connector footprints with 2x3 2.54mm Odd/Event 6-Pin IDC.
    The case connectors are 6 pin (inner) Male -> Female -> Male (outer)
2025-07-06 ERC Warnings: 7
    . Reworked Power section to flow from left to right.
    . Separated the Power switch connector from the external SPST + LED component.
    . Changed most NOT POPULATED external flags to Excluded from Simulation only. It gives a nice visual gray without exclusion from BOM.
2025-07-07 Added project specific symbol library Revision01.kicad_sym which now stores the STM symbol.
2025-07-07 ERC Warnings: 6
    . Fixed 100uF capacitor upstream of PMOS Switch
    . Fixed MPU-6500 floating pins
    . Fixed STM PA2, PA3 USART2 AIN overlap bug
    . Added ANT_Enable pin
    . Created Adafruit 3070 symbol, added SMA & Antenna component symbols.
2025-07-08 Condensed the bulk of symbol attributes.
2025-07-09 . Added 10nF filtering capacitor to remove high frequencies from travelling through cable. . Added Qty Multiplier factor for orders including receiver side compents (antenna, sma, 3070) . Removed TOD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
2025-07-09 Removed many redundant IDC cabling jumper symbols by using the Qty Multiplier field.
2025-07-09 Imported and verified functional strainAmplifier circuit from ALTIUM -> KICAD
2025-07-13 Improved documentation on LTSPICE schematics - Created WORD document containing documentation on all LTSPICE stimulations - Changed strainPower mosfet to NMOS <- subject to change - Redid clamping di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
    Having issues integrating amplifier schematic with clamping diode schematic.
2025-07-13 PMOS SWITCHING STIMULATION
2025-07-14 - Redo buck converter calculations - Maybe stimulate it. - Choose components for RC mosfet circuit - Verify MOSFET calculations - tried and changed PMOS type - Check fuse selection. Accounting for BU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
2025-07-16 some files were missed last commit
2025-07-28 re-re-re-re-re routed PCB
2025-07-29 . Changed ribbon connector pin standard, 1=GND, 2=Signal, 3=Power, 456=NC . Changed Buck Convertor footprint to IPC-C (hand solderable) . Created custom Adafruit 3070 footprint . Pointed MPU footprin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
2025-07-31 . Changed origin to bottom left . Resized edge cuts to be exactly (100mm)^2, with 1mm radius corners. . Placed 3.2mm_M3 mounting holes 6mm away from board edges; following the rule of thumb to space 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
2025-08-03 . Optimized pin selections for redistributed layout.
2025-08-04 . Repositioned Analog in Capacitors in trace path, symmetry in clamping diodes . Added vias for switching buck convertor
2025-08-07 . Completed KiCad track wiring. DRC Errors: 0 DRC Warnings: 55
2025-08-09 . Aligned connector fuse silkscreens . Placed silkscreen for antenna header . Changed antenna, stm nucleo board pin shapes so that GND is square.
2025-08-10 . Added ZeroOhmSwitch symbol & footprint for the Buck bypass . Adjusted holes to 5mm offset from edge for clearance from C8, C18 for standoffs . Added back silkscreen for PWR SWITCH headers . Minimiz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
2025-08-10 . Deleted & Ignored Altium History folder
2025-08-10 . Renamed StrainAmplifierV1 to just Amplifier . Removed autosave file . Attempt to remove git LFS support.
2025-08-13 . Split Hub symbol fields for Distributor Link/Part into DigiKey & AliExpress Link/Part in preparation for Mouser column.
2025-08-15 . Merged Amplifier & Hub libraries into "Lib" . Added Amplifier 6 pin IDC footprint . Finalized Amplifier layout & silkscreen
2025-08-16 . Fixed major BOM bug in Antenna, ordering correct Male Outer, Male Inner Part . Added Mouser column in Hub.
2025-08-17 . Made sure amplifier passive silk screen doesn't overlap pads . Added 6xAA battery holder to hub BOM . Exported gerbers, drl files .zip (PCBWay approved)
2025-08-17 . Added AliExpress estimates to BCIT Racing Invoice.
2025-08-18 Documentation cleanup
    Added comments on current usage.
    Cleaned up documentation folder as well as improved small details on it
    Cleaned up old LTSPICE stimulations
2025-08-20 neatened up silkscreen, added 0.1uF CAP to antenna
2025-08-20 . Reverted Hardware/ changes to last known good commit f7a44a23fed9aca3ce7036a9f440c4d810a77518
2025-08-25 initialized STM32CUBEIDE file with variables corresponding to schematic net labels
2025-08-27 Amplifier testing procedure started - initial test to make sure it works - beginning to test for real world electrical/mechanical conditions
2025-09-03 . Added QSpice ZXMP10A13F PMOS symbol from Diodes Incorporated
2025-09-04 . Changed battery measurement switch to 1/5 1/2 mA, uses the same components as the regular analog in chain . Added simulation for battery measurement "switch" . Checked DRC & ERC
2025-09-04 . Generated Product_2025-09-04.zip - Includes quotes from PCBWay, Digikey, Aliexpress
2025-09-05 small visual changes - put X on bypass 0 ohm resistor - do not populate on extra-battery type
2025-11-27 testing results for 5V-rails, voltage-divider, and buffer for board1
2025-12-14 was able to verify second board works up to 1KHz, however test results are very inconsistent.
2025-12-15 (hardware Testing) attached strain gauge onto board 1 for basic testing
    - offset voltage is about 1.44V rather than 1.67V
    - bent strain gauge and saw change in voltage
2026-02-02 . Added source code for Operator/ Windows Visual Studio Solution . Added source code for Firmware_CubeMX/ Blinky
2026-02-02 . Tested 500 kbps serial (working) using CoolTerm . Fixed default GPIO settings in CubeMX.
2026-02-03 . Added hello_world.xlsx writer example in Operator. (Built libxlsxwriter, zlib)
2026-02-10 (Renamed files to be consistent with uppercase naming convention)
2026-02-12 . Added ExcelService PublishData Demo (The writer library is unfortunately, kind of one-shot only) . Added Version includes
2026-02-26 . Fixed a default case fallthrough bug with StateMachine.h, and polished it
2026-03-12 Reworked DeviceService.cc to close and re-open the COM port successfully, despite unplugging and plugging.
